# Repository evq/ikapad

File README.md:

# ikapad
Electronics for a homemade DDR pad.

Uses four load cells per button configured in a full bridge measured by a HX711
amplifier and interfaced with a maple mini clone.

## Load Cell Full Bridge

Shared on [OSH Park.](https://oshpark.com/shared_projects/TjpPaXwd)

### BOM

| Name           | Description                 | MPN        |
|----------------|-----------------------------|------------|
| P1, P2, P3, P4 | MOLEX PICOBLADE 3POS 1.25MM | 0532610371 |
| P5             | TE CONN FPC 4POS 1.00MM     | 84952-4    |

## Amplifier Connector

Shared on [OSH Park.](https://oshpark.com/shared_projects/CgzNqpg0)

### BOM

| Name           | Description                 | MPN        |
|----------------|-----------------------------|------------|
| P1             | TE CONN FPC 4POS 1.00MM     | 84952-4    |

## Controller Half Shield

Shared on [OSH Park.](https://oshpark.com/shared_projects/OMPG9A2k)

### BOM

| Name           | Description          |
|----------------|----------------------|
| A1, A2, A3, A4 | HX711 BREAKOUT BOARD |
| A5             | BAITE MAPLE MINI     |

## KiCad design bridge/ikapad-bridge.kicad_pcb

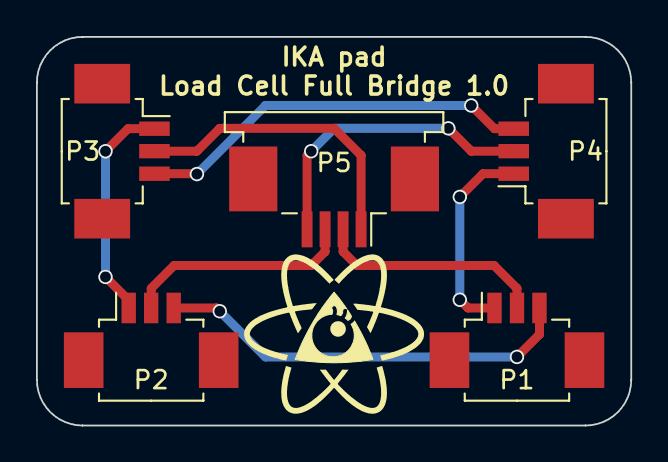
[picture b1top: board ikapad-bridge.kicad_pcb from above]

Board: 2 copper layers, 33.0 x 21.6 mm, 6 parts (0 on the bottom side), 8 nets.

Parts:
P1, P2, P3, P4: Molex_PicoBlade_53261-0371_03x1.25mm_Angled
P5: TE_84952-4_1x04-1MP_P1.0mm_Horizontal
svg2mod: G***; cutelab_1cm

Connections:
E+: P3.2, P5.1
E-: P1.2, P5.2
unnamed: P1.1, P4.1
unnamed: P1.3, P2.3
unnamed: P2.1, P3.1
unnamed: P3.3, P4.3
S+: P4.2, P5.4
S-: P2.2, P5.3

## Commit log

2018-06-18 ikapad electronics v1
2018-06-18 add OSH PARK links
2018-06-18 tweak spacing
